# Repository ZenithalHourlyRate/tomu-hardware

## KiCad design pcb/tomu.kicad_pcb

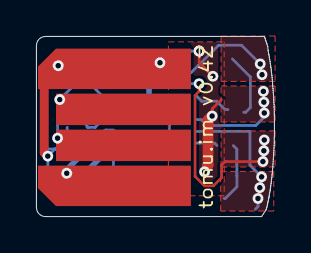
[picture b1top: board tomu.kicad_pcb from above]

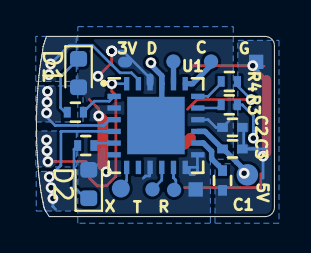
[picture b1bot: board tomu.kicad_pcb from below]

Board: 2 copper layers, 13.2 x 10.0 mm, 16 parts (15 on the bottom side), 17 nets.

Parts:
C1, C2: 1uF, 10V, X5R, 0402; C_0402
C3: 4.7uF, 6.3V, X5R, 0402; C_0402
D1: LED Green 0603; LED_0603_1608Metric
D2: LED, Red, 0603; LED_0603_1608Metric
P1: USART0; pads-1x3-slim
P2: DEBUG; pads-1x3
P3: USB-PCB
P4: RESET_PAD; pads-1x1
P5: 5V_PAD; pads-1x1
P6: 3V_PAD; pads-1x1
R1, R2: 100 Ohm, 1%, 1/16W, 0402; R_0402
R3, R4: 15 Ohm, 1%, 1/16W, 0402; R_0402
U1: EFM32HG309; QFN-24-1EP_5x5mm_Pitch0.65mm

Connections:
+3V3: C2.1, D1.2 (A), D2.2 (A), P1.1, P6.1, U1.2 (IOVDD_0), U1.9 (AVDD_2), U1.12 (AVDD_0), U1.13 (VDD_DREG), U1.16 (USB_VREG0), U1.22 (IOVDD_5)
/DBG_SWCLK: P2.2, U1.19 (PF0)
/DBG_SWDIO: P2.3, U1.20 (PF1)
/DEC: C1.2, U1.14 (DECOUPLE)
/LED0: R2.2, U1.5 (PB7)
/LED1: R1.1, U1.1 (PA0)
/LEU0_RX: P1.2, U1.11 (PB14)
/LEU0_TX: P1.3, U1.10 (PB13)
/RUSB_D+: R4.2, U1.18 (PC15)
/RUSB_D-: R3.2, U1.17 (PC14)
/USB_5V: C3.1, P3.1 (VCC), P5.1, U1.15 (USB_VREGI)
/USB_D+: P3.3 (D+), R4.1
/USB_D-: P3.2 (D-), R3.1
//RESET: P4.1, U1.7 (~RESET)
GND: C1.1, C2.2, C3.2, P2.1, P3.4 (GND), U1.21 (PF2), U1.25 (VSS)
unnamed: D1.1 (K), R1.2
unnamed: D2.1 (K), R2.1

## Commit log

2022-02-15 v0.4Z: width 1cm, led 0603
2022-02-15 eliminate edge.cut DRC
2022-02-15 DRC: fix silkscreen

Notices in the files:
pcb/tomu.kicad_pcb:
License: CC-BY-SA 4.0 or TAPR
